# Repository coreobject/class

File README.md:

This is the repository for the class.

The syllabus and simple code is here. Larger projects will get their own repos.

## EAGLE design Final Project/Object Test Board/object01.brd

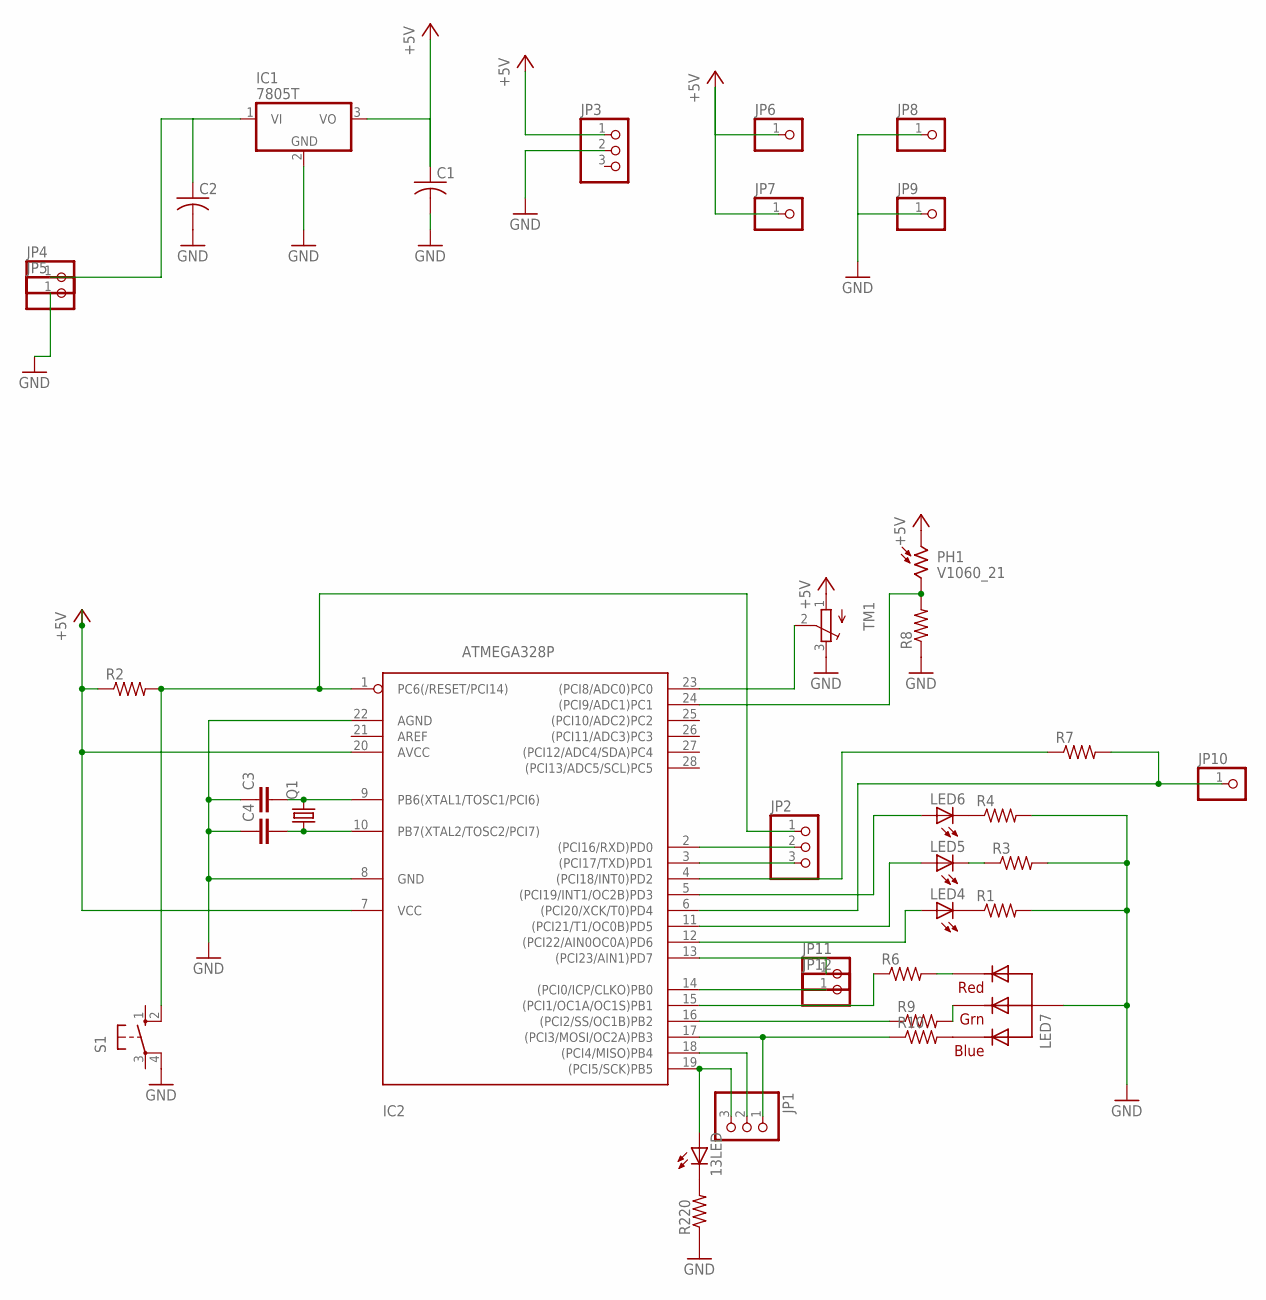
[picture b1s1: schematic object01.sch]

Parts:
13LED: LED5MM
C1, C2: C-US050-024X044; C050-024X044
C3, C4: C-EU025-024X044; C025-024X044
IC1: 7805T; TO220H
IC2: ATMEGA328P; DIL28-3
JP1, JP2, JP3: PINHD-1X3CB; 1X03-CLEANBIG
JP4, JP5, JP6, JP7, JP8, JP9, JP10, JP11, JP12: PINHD-1X1; 1X01
LED4, LED5, LED6: LED5MM
LED7: RGBLED_CA-5MM; LED5MMRGB
PH1: V1060_21; TO-5_V10
Q1: CRYSTALHC49U-V; HC49U-V
R1, R3, R4, R6, R7, R8, R9, R10, R220: R-US_0207/10; 0207/10
R2: R-US_0204/5; 0204/5
S1: 10-XX; B3F-10XX
TM1: TRIMPOT3386; TRIM-3386

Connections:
+5V: C1.1, IC1.3 (VO), IC2.7 (VCC), IC2.20 (AVCC), JP3.1, JP6.1, JP7.1, PH1.1, R2.1, TM1.1 (A)
GND: C1.2, C2.2, C3.1, C4.1, IC1.2 (GND), IC2.8 (GND), IC2.22 (AGND), JP3.2, JP5.1, JP8.1, JP9.1, LED7.2 (VCC), R1.2, R3.2, R4.2, R8.1, R220.1, S1.4 (P1), TM1.3 (E)
unnamed: C2.1, IC1.1 (VI), JP4.1
unnamed: C3.2, IC2.9 (PB6(XTAL1/TOSC1/PCI6)), Q1.2
unnamed: C4.2, IC2.10 (PB7(XTAL2/TOSC2/PCI7)), Q1.1
unnamed: IC2.17 ((PCI3/MOSI/OC2A)PB3), JP1.1, R10.1
unnamed: IC2.18 ((PCI4/MISO)PB4), JP1.2
unnamed: 13LED.A, IC2.19 ((PCI5/SCK)PB5), JP1.3
unnamed: IC2.2 ((PCI16/RXD)PD0), JP2.2
unnamed: IC2.3 ((PCI17/TXD)PD1), JP2.3
unnamed: IC2.1 (PC6(/RESET/PCI14)), JP2.1, R2.2, S1.2 (S1)
unnamed: LED7.1 (RED), R6.2
unnamed: LED7.3 (GREEN), R9.2
unnamed: LED5.K (C), R3.1
unnamed: LED4.K (C), R1.1
unnamed: LED6.K (C), R4.1
unnamed: IC2.14 ((PCI0/ICP/CLKO)PB0), JP12.1
unnamed: IC2.5 ((PCI19/INT1/OC2B)PD3), LED6.A
unnamed: IC2.11 ((PCI21/T1/OC0B)PD5), LED5.A
unnamed: IC2.12 ((PCI22/AIN0OC0A)PD6), LED4.A
unnamed: IC2.23 ((PCI8/ADC0)PC0), TM1.2 (S)
unnamed: IC2.24 ((PCI9/ADC1)PC1), PH1.2, R8.2
unnamed: IC2.13 ((PCI23/AIN1)PD7), JP11.1
unnamed: IC2.4 ((PCI18/INT0)PD2), R7.1
unnamed: IC2.6 ((PCI20/XCK/T0)PD4), JP10.1, R7.2
unnamed: LED7.4 (BLUE), R10.2
unnamed: 13LED.K (C), R220.2
unnamed: IC2.15 ((PCI1/OC1A/OC1S)PB1), R6.1
unnamed: IC2.16 ((PCI2/SS/OC1B)PB2), R9.1

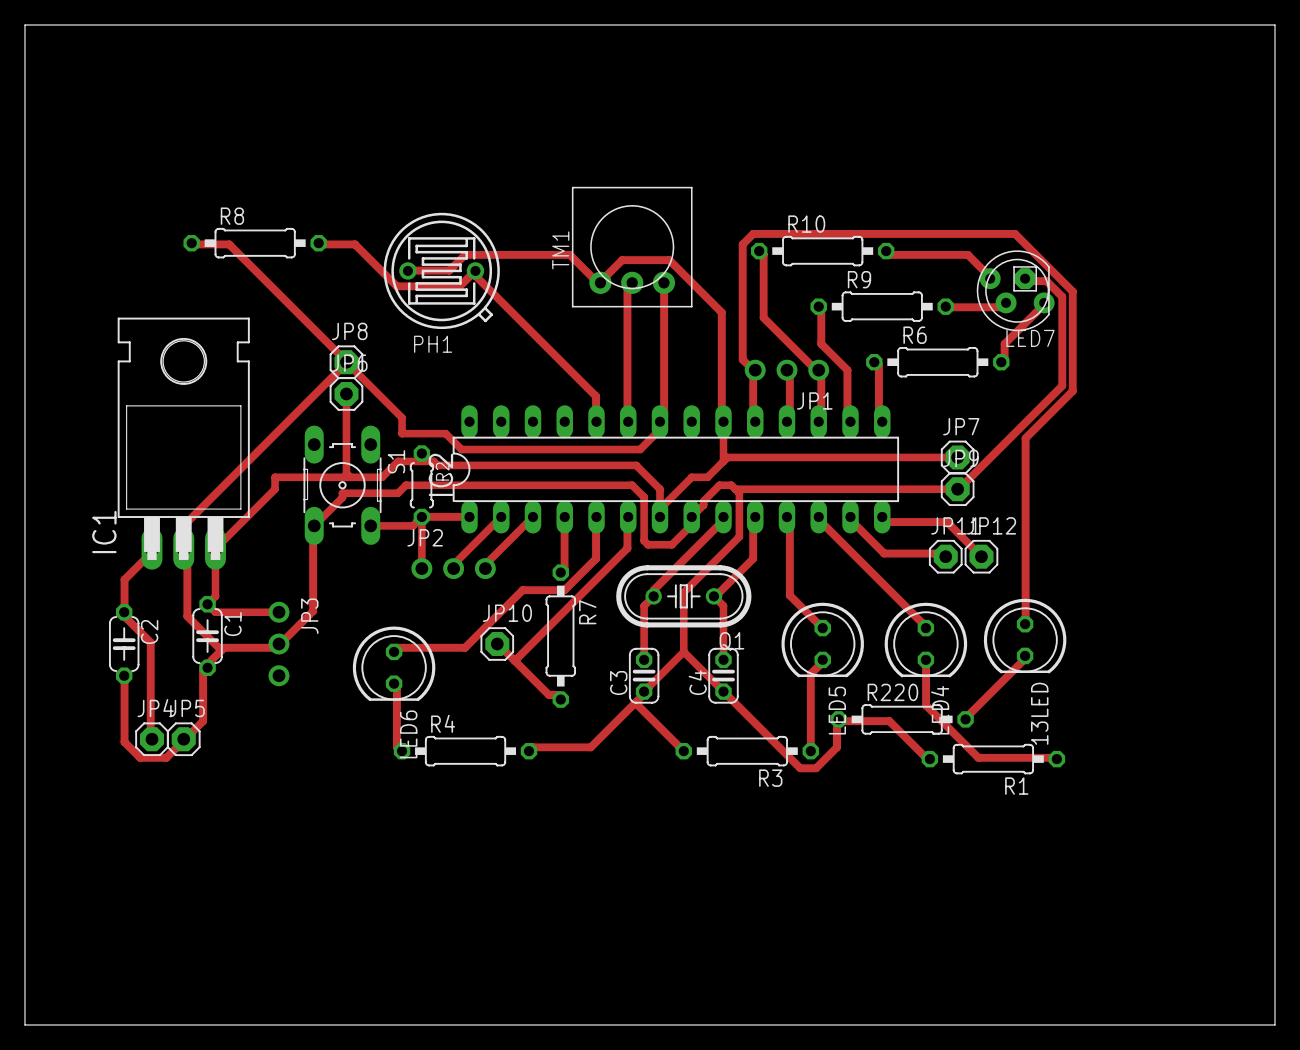
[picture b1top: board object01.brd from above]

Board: 1 copper layer, 100.0 x 80.0 mm, 37 parts (0 on the bottom side), 29 nets.

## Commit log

2015-09-18 adding main file.
2015-09-18 made some edits for GFM
2015-09-18 added images
2015-09-18 change dirs and names
2015-09-18 added week 3
2015-09-18 added 3-1
2015-09-18 circuit diagram
2015-09-18 changed week 3-2
2015-09-24 created folders and Advanced Programming File
2015-09-24 Made the sketch Earth friendly!
    The LED’s now light up only when the photoresistor senses that it is
    dark saving tooons of electricity!
2015-09-24 added light sensor
2015-09-24 added pot to adjust sensetivity
2015-09-24 created advanced 2
2015-09-24 button
2015-09-24 exit states
2015-09-24 added comments
2015-10-06 added week 5
2015-10-08 comment on project 2
2015-10-22 updated schedule
2015-10-22 edited 10/22
2015-10-23 test working copy app
2015-10-30 added mini virtual pet
2015-11-11 added buildyourownarduino and updated syllabus
2015-11-11 updated mini virtual pet and build your own arduino
2015-11-19 updated schedule and final project
2015-12-02 added final project
2015-12-02 formatting
2015-12-02 added eagle file
2015-12-02 added pinout diagram link
2015-12-03 added test board
2015-12-04 small edits to board
